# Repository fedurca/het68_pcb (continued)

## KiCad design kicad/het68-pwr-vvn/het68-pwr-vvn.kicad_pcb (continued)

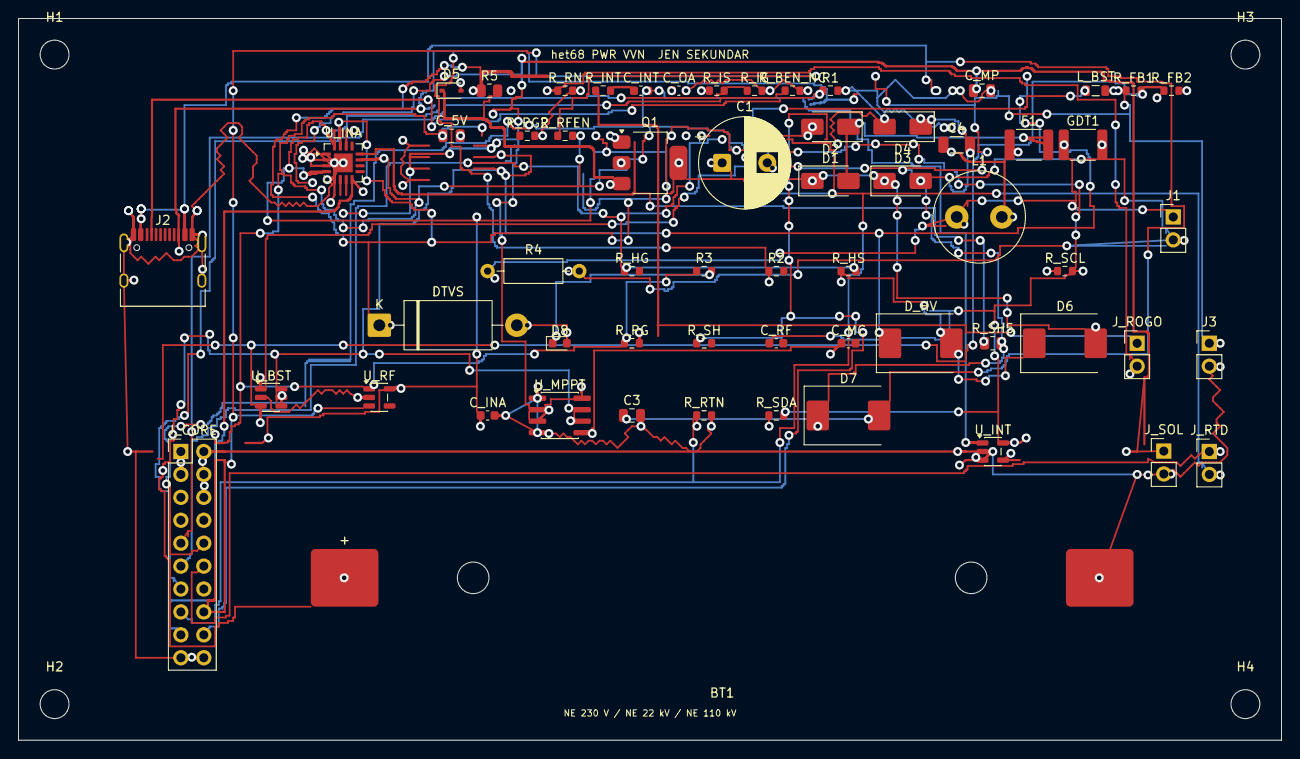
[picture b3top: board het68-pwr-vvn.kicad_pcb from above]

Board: 2 copper layers, 140.0 x 80.0 mm, 64 parts (0 on the bottom side), 35 nets.

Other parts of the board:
H1, H2, H3, H4: M3; MountingHole_3.2mm_M3

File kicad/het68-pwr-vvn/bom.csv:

Ref,Value,Footprint,MPN,LCSC
J1,CT_SEC,Connector_PinHeader_2.54mm:PinHeader_1x02_P2.54mm_Vertical,"sekundar CT, NE sit",
R4,100,Resistor_THT:R_Axial_DIN0207_L6.3mm_D2.5mm_P10.16mm_Horizontal,100R THT burden,
GDT1,GDT,Fuse:Fuse_1812_4532Metric,GDT secondary,
L1,470uH,Inductor_THT:L_Radial_D10.0mm_P5.00mm_Fastron_07P,470uH radial,
C4,1u/100V,Capacitor_SMD:C_1206_3216Metric,1uF 100V X7R LC,
F1,0.5A,Fuse:Fuse_1812_4532Metric,polyfuse 1812 0.5 A,
D1,SS14,Diode_SMD:D_SMA,SS14,
D2,SS14,Diode_SMD:D_SMA,SS14,
D3,SS14,Diode_SMD:D_SMA,SS14,
D4,SS14,Diode_SMD:D_SMA,SS14,
C1,470u/50V,Capacitor_THT:CP_Radial_D10.0mm_P5.00mm,electrolytic 470u 50V,
Q1,X0202MN,Package_TO_SOT_SMD:SOT-223,X0202MN,
D5,BZX84-C24,Diode_SMD:D_SOD-323,BZX84-C24,
R5,1k,Resistor_SMD:R_0805_2012Metric,RC0805FR-071KL,
DTVS,15KP36A,Diode_THT:D_DO-201_P15.24mm_Horizontal,15KP36A,
D6,SS34,Diode_SMD:D_SMC,SS34,
J_ROGO,ROGOWSKI,Connector_PinHeader_2.54mm:PinHeader_1x02_P2.54mm_Vertical,"Rogowski secondary, NE sit",
R_RN,0,Resistor_SMD:R_0603_1608Metric,RC0603FR-070RL,
R_INT,10k,Resistor_SMD:R_0603_1608Metric,RC0603FR-0710KL,
C_INT,100n,Capacitor_SMD:C_0603_1608Metric,CL10B104KB8NNNC,
U_INT,MCP6001,Package_TO_SOT_SMD:SOT-23-5,MCP6001T-OT,
C_OA,100n,Capacitor_SMD:C_0603_1608Metric,CL10B104KB8NNNC,
R_IS,10k,Resistor_SMD:R_0603_1608Metric,RC0603FR-0710KL,
R_IG,10k,Resistor_SMD:R_0603_1608Metric,RC0603FR-0710KL,
R_BEN_NC,100k,Resistor_SMD:R_0603_1608Metric,RC0603FR-07100KL,
J2,USB_C,Connector_USB:USB_C_Receptacle_HRO_TYPE-C-31-M-12,TYPE-C-31-M-12,C165948
R1,5.1k,Resistor_SMD:R_0603_1608Metric,RC0603FR-075K1L,
R2,5.1k,Resistor_SMD:R_0603_1608Metric,RC0603FR-075K1L,
D7,SS34,Diode_SMD:D_SMC,SS34,
C3,10u,Capacitor_SMD:C_0805_2012Metric,CL21A106KOQNNNE,
J_SOL,SOLAR,Connector_PinHeader_2.54mm:PinHeader_1x02_P2.54mm_Vertical,panel Voc 6-18 V,
U_MPPT,CN3791,Package_SO:SOIC-8_3.9x4.9mm_P1.27mm,CN3791,
C_MP,10u,Capacitor_SMD:C_0805_2012Metric,CL21A106KOQNNNE,
C_MC,100n,Capacitor_SMD:C_0603_1608Metric,CL10B104KB8NNNC,
D_HV,SS34,Diode_SMD:D_SMC,SS34,
BT1,21700,het68:Keystone_1122_21700,Keystone 1122,
U_BST,FP6291,Package_TO_SOT_SMD:SOT-23-6,FP6291,
L_BST,10uH,Inductor_SMD:L_0805_2012Metric,10uH boost,
R_FB1,100k,Resistor_SMD:R_0603_1608Metric,RC0603FR-07100KL,
R_FB2,20k,Resistor_SMD:R_0603_1608Metric,RC0603FR-0720KL,
C_5V,10u,Capacitor_SMD:C_0805_2012Metric,CL21A106KOQNNNE,
R_PG,10k,Resistor_SMD:R_0603_1608Metric,RC0603FR-0710KL,
R_PG2,10k,Resistor_SMD:R_0603_1608Metric,RC0603FR-0710KL,
U_RF,AP2112K-3.3,Package_TO_SOT_SMD:SOT-23-5,AP2112K-3.3TRG1,
R_RFEN,10k,Resistor_SMD:R_0603_1608Metric,RC0603FR-0710KL,
C_RF,1u,Capacitor_SMD:C_0603_1608Metric,CL10A105KA8NNNC,
U_INA,INA3221,Package_DFN_QFN:Texas_RGV0016A_VQFN-16-1EP_4x4mm_P0.65mm_EP2.1x2.1mm,INA3221AIRGVR,C181255
R_SH5,0.1,Resistor_SMD:R_0805_2012Metric,RC0805FR-070R1L,
C_INA,100n,Capacitor_SMD:C_0603_1608Metric,CL10B104KB8NNNC,
R_HS,10k,Resistor_SMD:R_0603_1608Metric,RC0603FR-0710KL,
R_HG,10k,Resistor_SMD:R_0603_1608Metric,RC0603FR-0710KL,
J_RTD,PT1000,Connector_PinHeader_2.54mm:PinHeader_1x02_P2.54mm_Vertical,PT1000 on conductor,
R_RTN,0,Resistor_SMD:R_0603_1608Metric,RC0603FR-070RL,
J_CORE,J_CORE,Connector_PinHeader_2.54mm:PinHeader_2x10_P2.54mm_Vertical,interconnect 2x10,
R_SH,0,Resistor_SMD:R_0603_1608Metric,RC0603FR-070RL,
R_SDA,4.7k,Resistor_SMD:R_0603_1608Metric,RC0603FR-074K7L,
R_SCL,4.7k,Resistor_SMD:R_0603_1608Metric,RC0603FR-074K7L,
D8,LED,LED_SMD:LED_0603_1608Metric,LED 0603,
R3,2.2k,Resistor_SMD:R_0603_1608Metric,RC0603FR-072K2L,
J3,VOUT,Connector_PinHeader_2.54mm:PinHeader_1x02_P2.54mm_Vertical,5V lab,

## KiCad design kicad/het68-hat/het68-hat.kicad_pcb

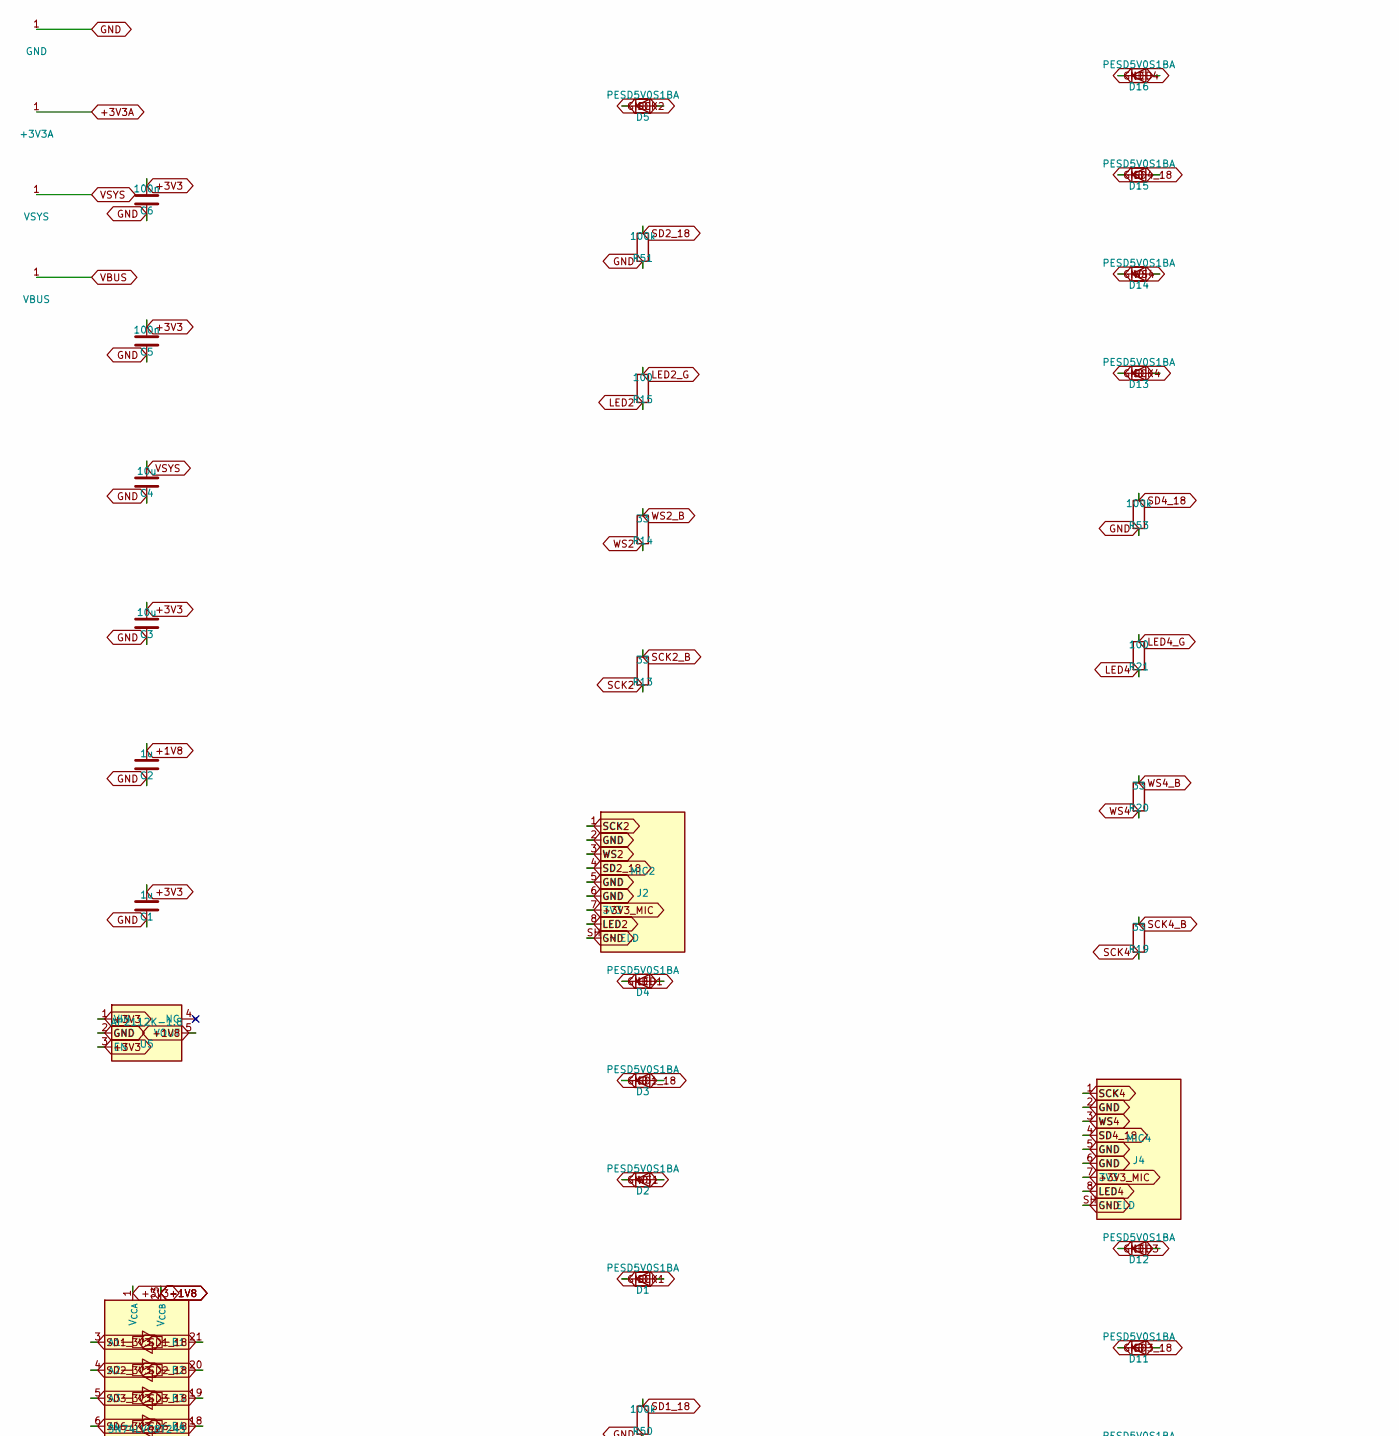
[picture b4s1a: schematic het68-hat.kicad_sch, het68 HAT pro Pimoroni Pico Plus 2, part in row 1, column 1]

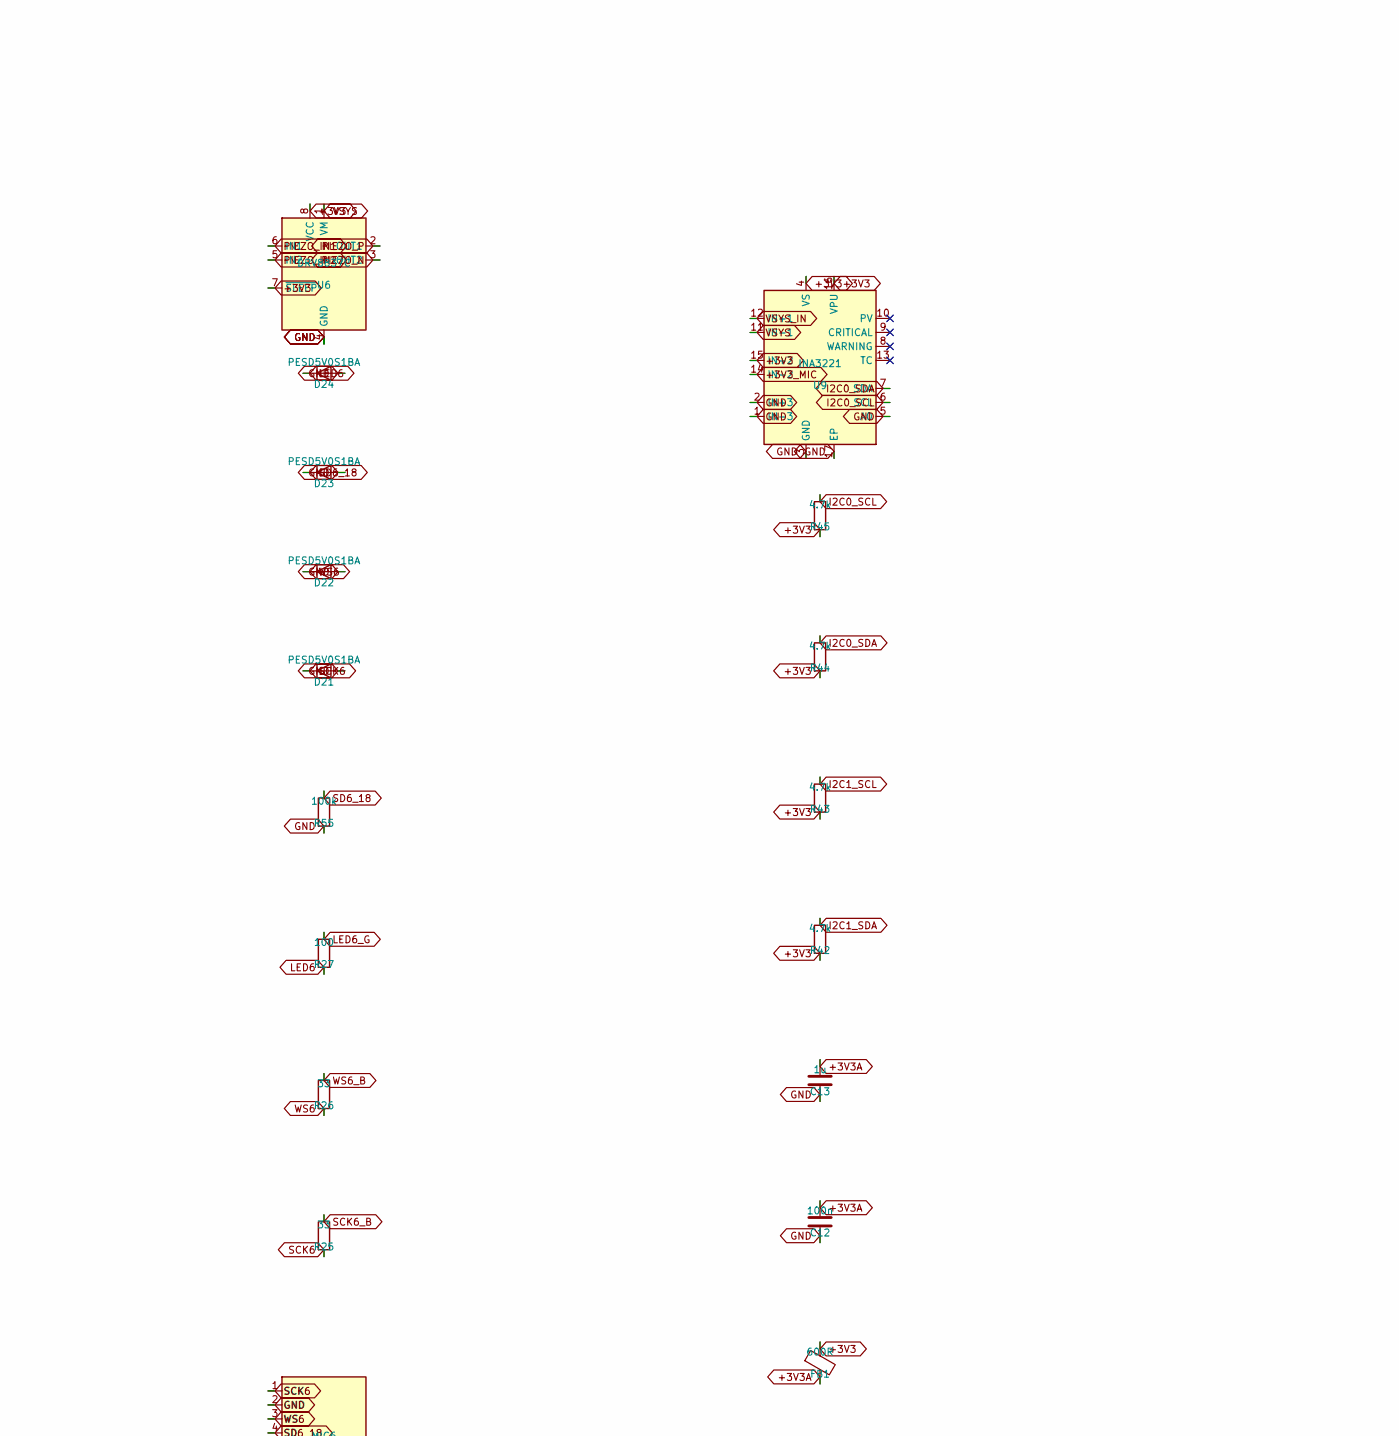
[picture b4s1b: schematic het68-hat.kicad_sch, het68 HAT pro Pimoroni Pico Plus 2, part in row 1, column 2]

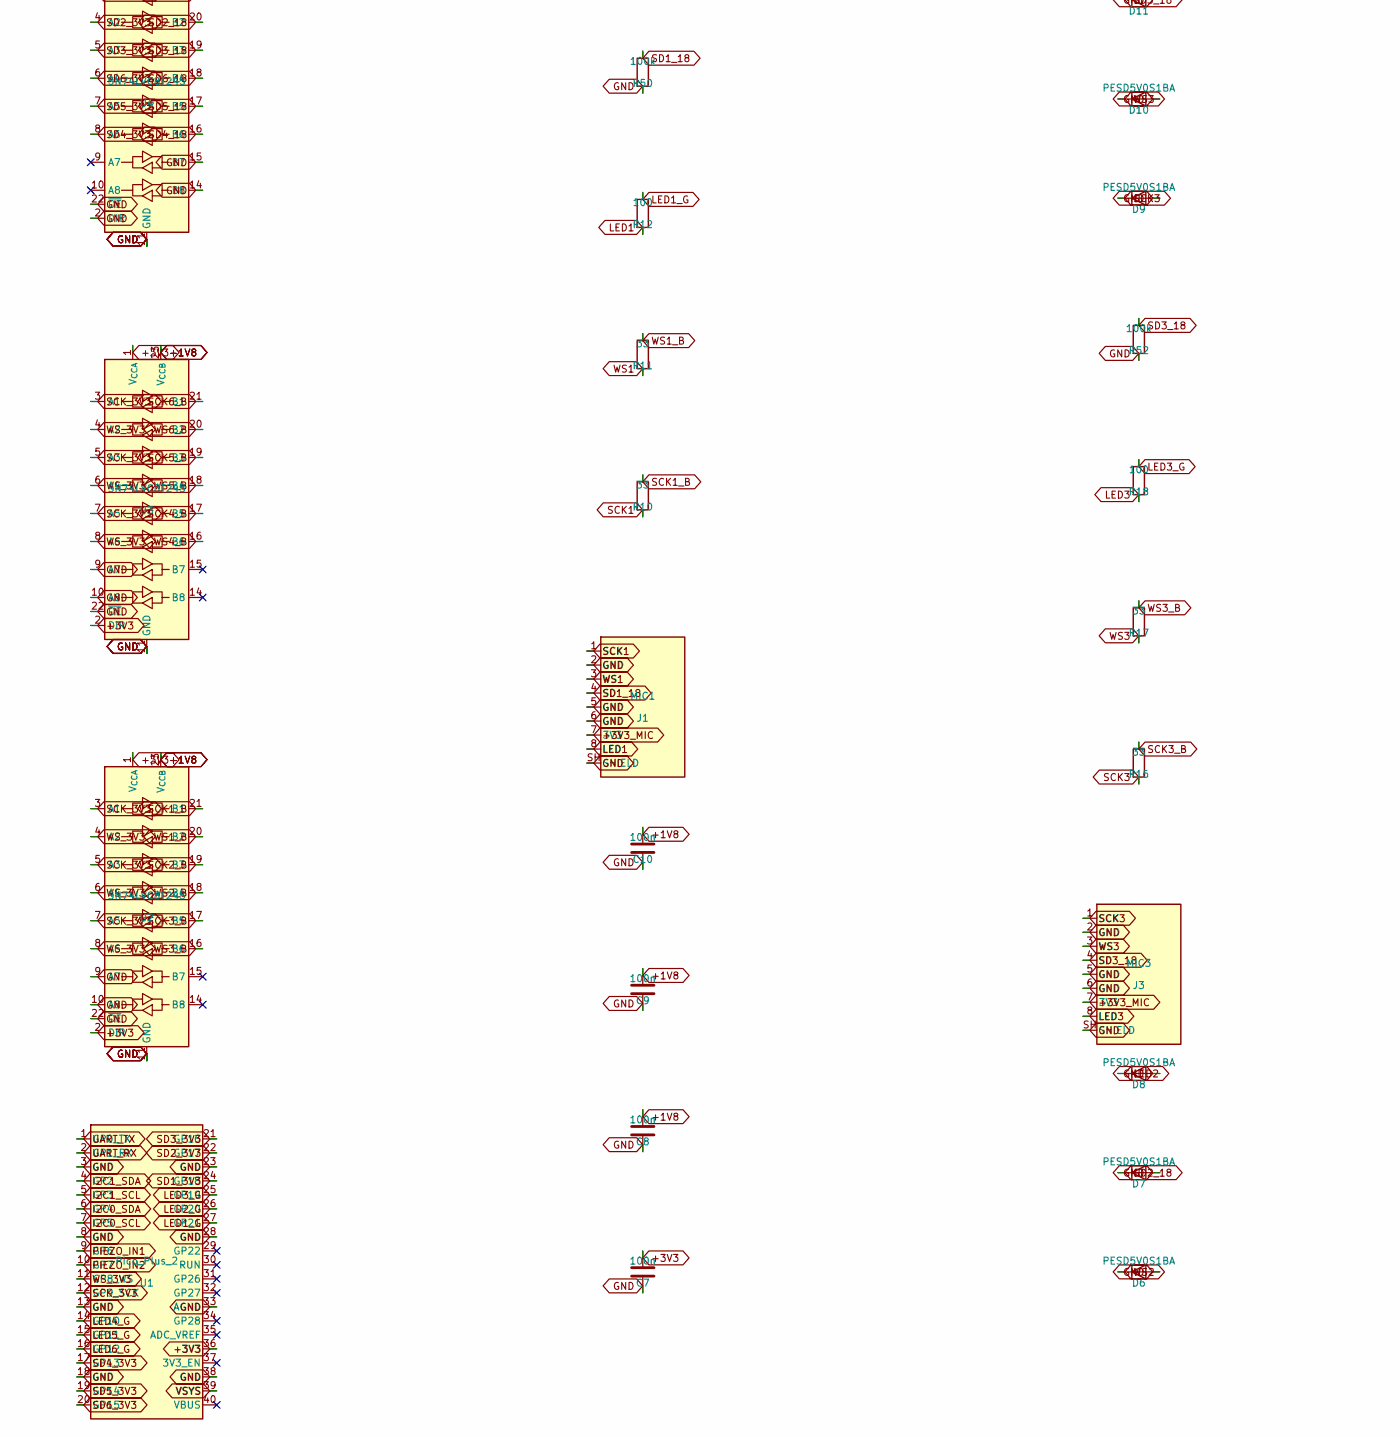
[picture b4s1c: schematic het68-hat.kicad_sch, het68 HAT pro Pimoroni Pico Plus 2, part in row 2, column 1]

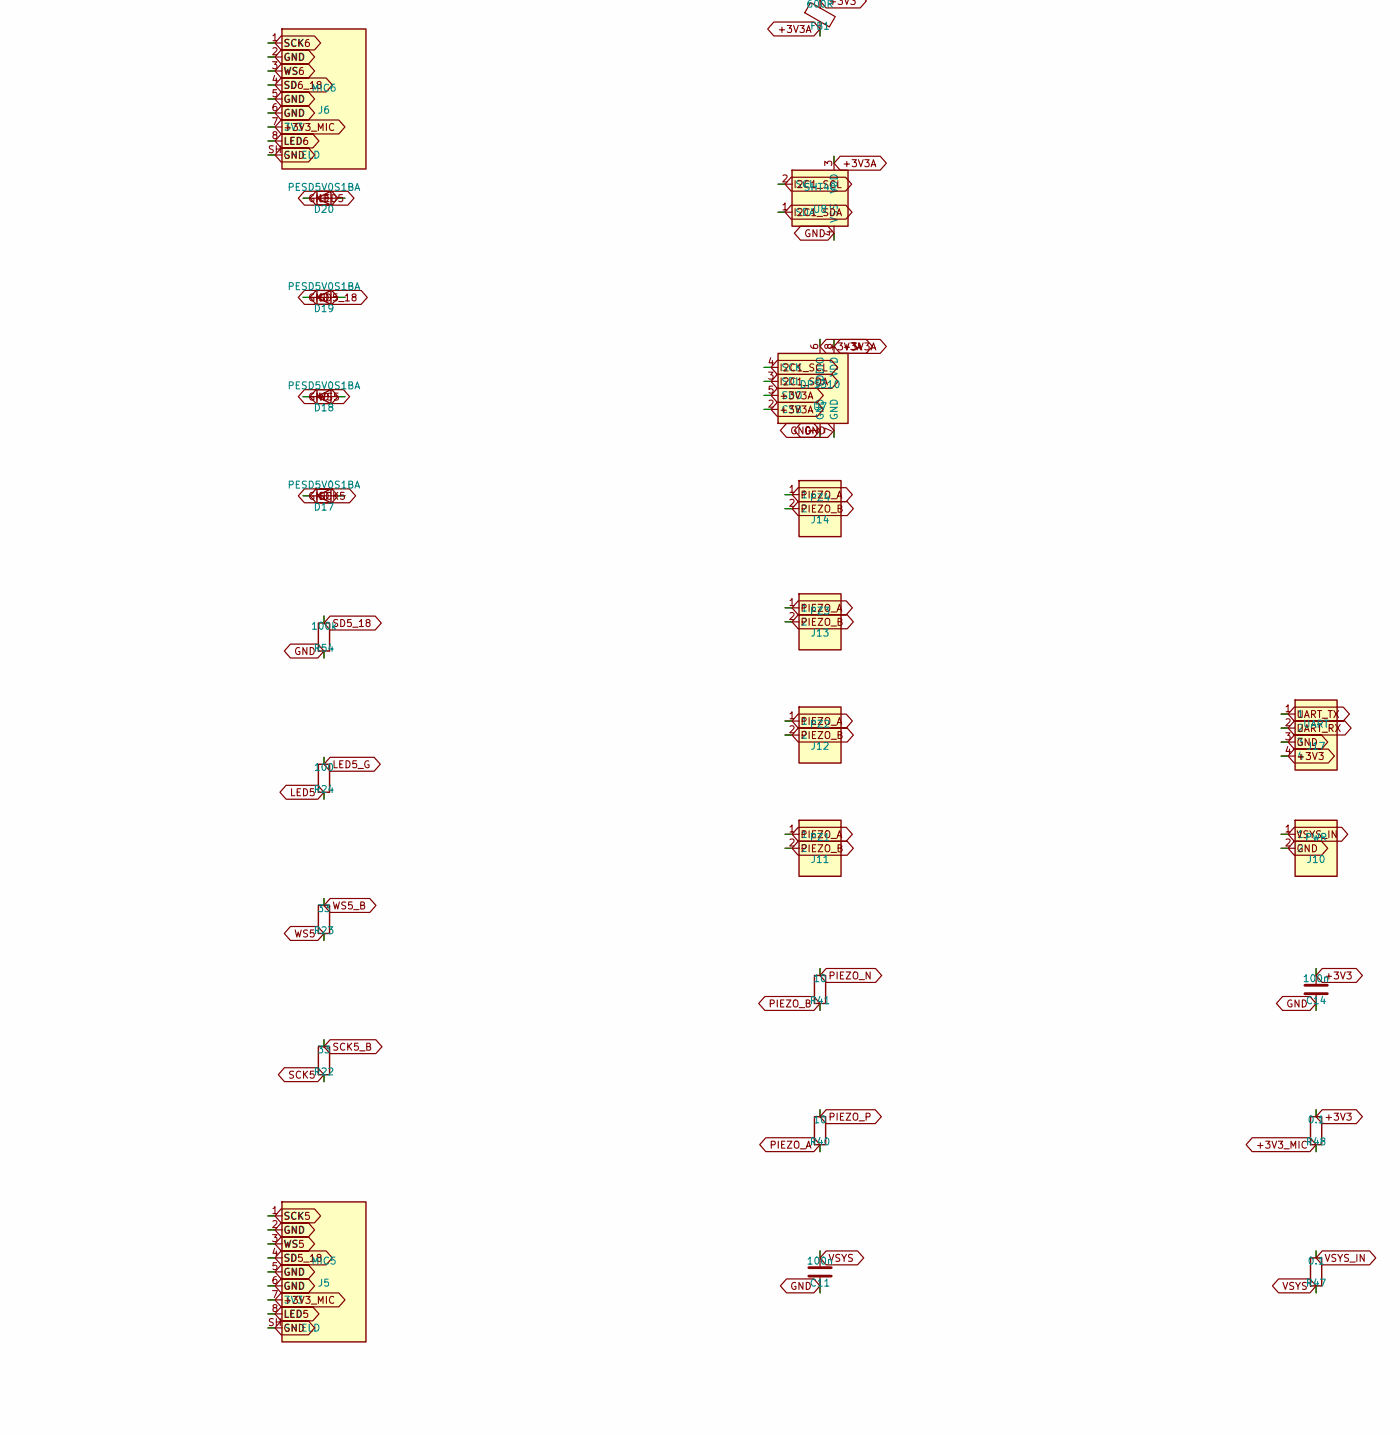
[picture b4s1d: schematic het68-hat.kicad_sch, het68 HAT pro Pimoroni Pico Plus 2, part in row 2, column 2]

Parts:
C1, C2, C13: 1u; C_0603_1608Metric; MPN CL10A105KA8NNNC
C3, C4: 10u; C_0805_2012Metric; MPN CL21A106KOQNNNE
C5, C6, C7, C8, C9, C10, C11, C12, C14: 100n; C_0603_1608Metric; MPN CL10B104KB8NNNC
D1, D2, D3, D4, D5, D6, D7, D8, D9, D10, D11, D12, D13, D14, D15, D16, D17, D18, D19, D20, D21, D22, D23, D24: PESD5V0S1BA; D_SOD-323; MPN PESD5V0S1BA,115
FB1: 600R; L_0603_1608Metric; MPN BLM18PG601SN1D
J1: MIC1; RJ45_RJHSE5380_het68; MPN RJHSE-5380 (8P8C, bez magnetik)
J2: MIC2; RJ45_RJHSE5380_het68; MPN RJHSE-5380 (8P8C, bez magnetik)
J3: MIC3; RJ45_RJHSE5380_het68; MPN RJHSE-5380 (8P8C, bez magnetik)
J4: MIC4; RJ45_RJHSE5380_het68; MPN RJHSE-5380 (8P8C, bez magnetik)
J5: MIC5; RJ45_RJHSE5380_het68; MPN RJHSE-5380 (8P8C, bez magnetik)
J6: MIC6; RJ45_RJHSE5380_het68; MPN RJHSE-5380 (8P8C, bez magnetik)
J10: PWR; PinHeader_1x02_P2.54mm_Vertical; MPN PinHeader 1x2
J11: PZ1; PinHeader_1x02_P2.54mm_Vertical; MPN PinHeader 1x2
J12: PZ2; PinHeader_1x02_P2.54mm_Vertical; MPN PinHeader 1x2
J13: PZ3; PinHeader_1x02_P2.54mm_Vertical; MPN PinHeader 1x2
J14: PZ4; PinHeader_1x02_P2.54mm_Vertical; MPN PinHeader 1x2
J17: UART; PinHeader_1x04_P2.54mm_Vertical; MPN PinHeader 1x4
R10, R11, R13, R14, R16, R17, R19, R20, R22, R23, R25, R26: 33; R_0603_1608Metric; MPN RC0603FR-0733RL
R12, R15, R18, R21, R24, R27: 100; R_0603_1608Metric; MPN RC0603FR-07100RL
R40, R41: 10; R_1206_3216Metric; MPN RC1206FR-0710RL
R42, R43, R44, R45: 4.7k; R_0603_1608Metric; MPN RC0603FR-074K7L
R47, R48: 0.1; R_0805_2012Metric; MPN RC0805FR-070R1L
R50, R51, R52, R53, R54, R55: 100k; R_0603_1608Metric; MPN RC0603FR-07100KL
U1: Pico_Plus_2; RaspberryPi_Pico_Common_THT; MPN Pimoroni Pico Plus 2
U2, U3, U4: SN74LVC8T245; TSSOP-24_4.4x7.8mm_P0.65mm; MPN SN74LVC8T245PWR
U5: AP2112K-1.8; SOT-23-5; MPN AP2112K-1.8TRG1
U6: DRV8837C; Texas_DSG0008A_WSON-8-1EP_2x2mm_P0.5mm_EP0.9x1.6mm; MPN DRV8837CDSGR
U7: DPS310; Bosch_LGA-8_2x2.5mm_P0.65mm_ClockwisePinNumbering; MPN DPS310
U8: SHT40; Sensirion_DFN-4_1.5x1.5mm_P0.8mm_SHT4x_NoCentralPad; MPN SHT40-AD1B-R2
U9: INA3221; Texas_RGV0016A_VQFN-16-1EP_4x4mm_P0.65mm_EP2.1x2.1mm; MPN INA3221AIRGVR

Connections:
+1V8: C2.1, C8.1, C9.1, C10.1, U2.23 (V_{CCB}), U2.24 (V_{CCB}), U3.23 (V_{CCB}), U3.24 (V_{CCB}), U4.23 (V_{CCB}), U4.24 (V_{CCB}), U5.5 (VOUT)
+3V3: C1.1, C3.1, C5.1, C6.1, C7.1, C14.1, FB1.1, J17.4, R42.2, R43.2, R44.2, R45.2, R48.1, U1.36 (3V3), U2.1 (V_{CCA}), U2.2 (DIR), U3.1 (V_{CCA}), U3.2 (DIR), U4.1 (V_{CCA}), U5.1 (VIN), U5.3 (EN), U6.7 (~SLEEP), U6.8 (VCC), U9.4 (VS), U9.15 (IN+2), U9.16 (VPU)
+3V3A: C12.1, C13.1, FB1.2, U7.2 (CSB), U7.5 (SDO), U7.6 (VDDIO), U7.8 (VDD), U8.3 (VDD)
+3V3_MIC: J1.7 (3V3), J2.7 (3V3), J3.7 (3V3), J4.7 (3V3), J5.7 (3V3), J6.7 (3V3), R48.2, U9.14 (IN-2)
GND: C1.2, C2.2, C3.2, C4.2, C5.2, C6.2, C7.2, C8.2, C9.2, C10.2, C11.2, C12.2, C13.2, C14.2, D1.2 (A), D2.2 (A), D3.2 (A), D4.2 (A), D5.2 (A), D6.2 (A), D7.2 (A), D8.2 (A), D9.2 (A), D10.2 (A), D11.2 (A), D12.2 (A), D13.2 (A), D14.2 (A), D15.2 (A), D16.2 (A), D17.2 (A), D18.2 (A), D19.2 (A), D20.2 (A), D21.2 (A), D22.2 (A), D23.2 (A), D24.2 (A), J1.2 (GND), J1.5 (GND), J1.6 (GND), J1.SH (SHIELD), J2.2 (GND), J2.5 (GND), J2.6 (GND), J2.SH (SHIELD), J3.2 (GND), J3.5 (GND), J3.6 (GND), J3.SH (SHIELD), J4.2 (GND), J4.5 (GND), J4.6 (GND), J4.SH (SHIELD), J5.2 (GND), J5.5 (GND), J5.6 (GND), J5.SH (SHIELD), J6.2 (GND), J6.5 (GND), J6.6 (GND), J6.SH (SHIELD), J10.2, J17.3, R50.2, R51.2, R52.2, R53.2, R54.2, R55.2, U1.3 (GND), U1.8 (GND), U1.13 (GND), U1.18 (GND), U1.23 (GND), U1.28 (GND), U1.33 (AGND), U1.38 (GND), U2.9 (A7), U2.10 (A8), U2.11 (GND), U2.12 (GND), U2.13 (GND), U2.22 (~OE), U3.9 (A7), U3.10 (A8), U3.11 (GND), U3.12 (GND), U3.13 (GND), U3.22 (~OE), U4.2 (DIR), U4.11 (GND), U4.12 (GND), U4.13 (GND), U4.14 (B8), U4.15 (B7), U4.22 (~OE), U5.2 (GND), U6.4 (GND), U6.9 (GND), U7.1 (GND), U7.7 (GND), U8.4 (VSS), U9.1 (IN-3), U9.2 (IN+3), U9.3 (GND), U9.5 (A0), U9.17 (EP)
I2C0_SCL: R45.1, U1.7 (GP5), U9.6 (SCL)
I2C0_SDA: R44.1, U1.6 (GP4), U9.7 (SDA)
I2C1_SCL: R43.1, U1.5 (GP3), U7.4 (SCK), U8.2 (SCL)
I2C1_SDA: R42.1, U1.4 (GP2), U7.3 (SDI), U8.1 (SDA)
LED1: D4.1 (K), J1.8 (LED), R12.2
LED1_G: R12.1, U1.27 (GP21)
LED2: D8.1 (K), J2.8 (LED), R15.2
LED2_G: R15.1, U1.26 (GP20)
LED3: D12.1 (K), J3.8 (LED), R18.2
LED3_G: R18.1, U1.25 (GP19)
LED4: D16.1 (K), J4.8 (LED), R21.2
LED4_G: R21.1, U1.14 (GP10)
LED5: D20.1 (K), J5.8 (LED), R24.2
LED5_G: R24.1, U1.15 (GP11)
LED6: D24.1 (K), J6.8 (LED), R27.2
LED6_G: R27.1, U1.16 (GP12)
PIEZO_A: J11.1, J12.1, J13.1, J14.1, R40.2
PIEZO_B: J11.2, J12.2, J13.2, J14.2, R41.2
PIEZO_IN1: U1.9 (GP6), U6.6 (IN1)
PIEZO_IN2: U1.10 (GP7), U6.5 (IN2)
PIEZO_N: R41.1, U6.3 (OUT2)
PIEZO_P: R40.1, U6.2 (OUT1)
SCK1: D1.1 (K), J1.1 (SCK), R10.2
SCK1_B: R10.1, U2.21 (B1)
SCK2: D5.1 (K), J2.1 (SCK), R13.2
SCK2_B: R13.1, U2.19 (B3)
SCK3: D9.1 (K), J3.1 (SCK), R16.2
SCK3_B: R16.1, U2.17 (B5)
SCK4: D13.1 (K), J4.1 (SCK), R19.2
SCK4_B: R19.1, U3.17 (B5)
SCK5: D17.1 (K), J5.1 (SCK), R22.2
SCK5_B: R22.1, U3.19 (B3)
SCK6: D21.1 (K), J6.1 (SCK), R25.2
SCK6_B: R25.1, U3.21 (B1)
SCK_3V3: U1.12 (GP9_SCK), U2.3 (A1), U2.5 (A3), U2.7 (A5), U3.3 (A1), U3.5 (A3), U3.7 (A5)
SD1_3V3: U1.24 (GP18), U4.3 (A1)
SD1_18: D3.1 (K), J1.4 (SD), R50.1, U4.21 (B1)
SD2_3V3: U1.22 (GP17), U4.4 (A2)
SD2_18: D7.1 (K), J2.4 (SD), R51.1, U4.20 (B2)
SD3_3V3: U1.21 (GP16), U4.5 (A3)
SD3_18: D11.1 (K), J3.4 (SD), R52.1, U4.19 (B3)
SD4_3V3: U1.17 (GP13), U4.8 (A6)
SD4_18: D15.1 (K), J4.4 (SD), R53.1, U4.16 (B6)
SD5_3V3: U1.19 (GP14), U4.7 (A5)
SD5_18: D19.1 (K), J5.4 (SD), R54.1, U4.17 (B5)
SD6_3V3: U1.20 (GP15), U4.6 (A4)
SD6_18: D23.1 (K), J6.4 (SD), R55.1, U4.18 (B4)
UART_RX: J17.2, U1.2 (GP1_RX)
UART_TX: J17.1, U1.1 (GP0_TX)
VSYS: C4.1, C11.1, R47.2, U1.39 (VSYS), U6.1 (VM), U9.11 (IN-1)
VSYS_IN: J10.1, R47.1, U9.12 (IN+1)
WS1: D2.1 (K), J1.3 (WS), R11.2
WS1_B: R11.1, U2.20 (B2)
WS2: D6.1 (K), J2.3 (WS), R14.2
WS2_B: R14.1, U2.18 (B4)
WS3: D10.1 (K), J3.3 (WS), R17.2
WS3_B: R17.1, U2.16 (B6)
WS4: D14.1 (K), J4.3 (WS), R20.2
WS4_B: R20.1, U3.16 (B6)
WS5: D18.1 (K), J5.3 (WS), R23.2
WS5_B: R23.1, U3.18 (B4)
WS6: D22.1 (K), J6.3 (WS), R26.2
WS6_B: R26.1, U3.20 (B2)
WS_3V3: U1.11 (GP8_WS), U2.4 (A2), U2.6 (A4), U2.8 (A6), U3.4 (A2), U3.6 (A4), U3.8 (A6)

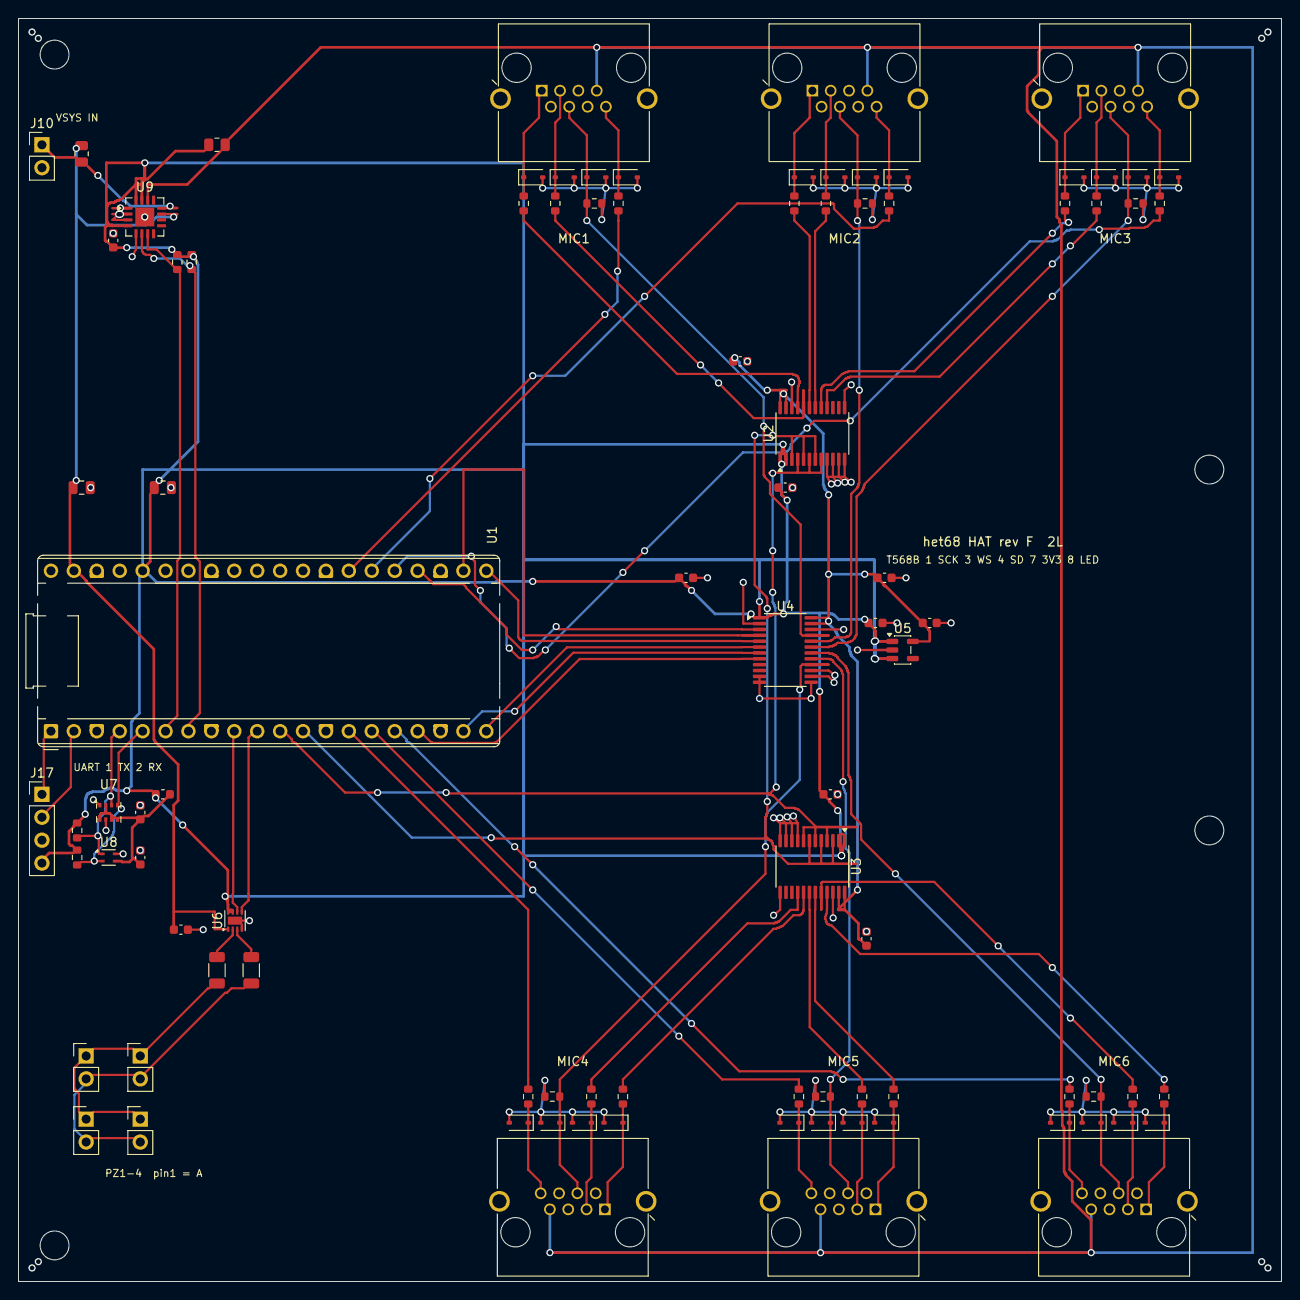
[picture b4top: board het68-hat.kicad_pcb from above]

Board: 2 copper layers, 140.0 x 140.0 mm, 96 parts (0 on the bottom side), 69 nets.

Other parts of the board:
H1, H2, H3, H4: M3; MountingHole_3.2mm_M3

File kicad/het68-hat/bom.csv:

Ref,Value,Footprint,MPN,LCSC
U1,Pico_Plus_2,Module:RaspberryPi_Pico_Common_THT,Pimoroni Pico Plus 2,
U2,SN74LVC8T245,Package_SO:TSSOP-24_4.4x7.8mm_P0.65mm,SN74LVC8T245PWR,C27643
U3,SN74LVC8T245,Package_SO:TSSOP-24_4.4x7.8mm_P0.65mm,SN74LVC8T245PWR,C27643
U4,SN74LVC8T245,Package_SO:TSSOP-24_4.4x7.8mm_P0.65mm,SN74LVC8T245PWR,C27643
U5,AP2112K-1.8,Package_TO_SOT_SMD:SOT-23-5,AP2112K-1.8TRG1,C176944
C1,1u,Capacitor_SMD:C_0603_1608Metric,CL10A105KA8NNNC,
C2,1u,Capacitor_SMD:C_0603_1608Metric,CL10A105KA8NNNC,
C3,10u,Capacitor_SMD:C_0805_2012Metric,CL21A106KOQNNNE,
C4,10u,Capacitor_SMD:C_0805_2012Metric,CL21A106KOQNNNE,
C5,100n,Capacitor_SMD:C_0603_1608Metric,CL10B104KB8NNNC,
C6,100n,Capacitor_SMD:C_0603_1608Metric,CL10B104KB8NNNC,
C7,100n,Capacitor_SMD:C_0603_1608Metric,CL10B104KB8NNNC,
C8,100n,Capacitor_SMD:C_0603_1608Metric,CL10B104KB8NNNC,
C9,100n,Capacitor_SMD:C_0603_1608Metric,CL10B104KB8NNNC,
C10,100n,Capacitor_SMD:C_0603_1608Metric,CL10B104KB8NNNC,
J1,MIC1,het68:RJ45_RJHSE5380_het68,"RJHSE-5380 (8P8C, bez magnetik)",C464586
R10,33,Resistor_SMD:R_0603_1608Metric,RC0603FR-0733RL,
R11,33,Resistor_SMD:R_0603_1608Metric,RC0603FR-0733RL,
R12,100,Resistor_SMD:R_0603_1608Metric,RC0603FR-07100RL,
R50,100k,Resistor_SMD:R_0603_1608Metric,RC0603FR-07100KL,
D1,PESD5V0S1BA,Diode_SMD:D_SOD-323,"PESD5V0S1BA,115",
D2,PESD5V0S1BA,Diode_SMD:D_SOD-323,"PESD5V0S1BA,115",
D3,PESD5V0S1BA,Diode_SMD:D_SOD-323,"PESD5V0S1BA,115",
D4,PESD5V0S1BA,Diode_SMD:D_SOD-323,"PESD5V0S1BA,115",
J2,MIC2,het68:RJ45_RJHSE5380_het68,"RJHSE-5380 (8P8C, bez magnetik)",C464586
R13,33,Resistor_SMD:R_0603_1608Metric,RC0603FR-0733RL,
R14,33,Resistor_SMD:R_0603_1608Metric,RC0603FR-0733RL,
R15,100,Resistor_SMD:R_0603_1608Metric,RC0603FR-07100RL,
R51,100k,Resistor_SMD:R_0603_1608Metric,RC0603FR-07100KL,
D5,PESD5V0S1BA,Diode_SMD:D_SOD-323,"PESD5V0S1BA,115",
D6,PESD5V0S1BA,Diode_SMD:D_SOD-323,"PESD5V0S1BA,115",
D7,PESD5V0S1BA,Diode_SMD:D_SOD-323,"PESD5V0S1BA,115",
D8,PESD5V0S1BA,Diode_SMD:D_SOD-323,"PESD5V0S1BA,115",
J3,MIC3,het68:RJ45_RJHSE5380_het68,"RJHSE-5380 (8P8C, bez magnetik)",C464586
R16,33,Resistor_SMD:R_0603_1608Metric,RC0603FR-0733RL,
R17,33,Resistor_SMD:R_0603_1608Metric,RC0603FR-0733RL,
R18,100,Resistor_SMD:R_0603_1608Metric,RC0603FR-07100RL,
R52,100k,Resistor_SMD:R_0603_1608Metric,RC0603FR-07100KL,
D9,PESD5V0S1BA,Diode_SMD:D_SOD-323,"PESD5V0S1BA,115",
D10,PESD5V0S1BA,Diode_SMD:D_SOD-323,"PESD5V0S1BA,115",
D11,PESD5V0S1BA,Diode_SMD:D_SOD-323,"PESD5V0S1BA,115",
D12,PESD5V0S1BA,Diode_SMD:D_SOD-323,"PESD5V0S1BA,115",
J4,MIC4,het68:RJ45_RJHSE5380_het68,"RJHSE-5380 (8P8C, bez magnetik)",C464586
R19,33,Resistor_SMD:R_0603_1608Metric,RC0603FR-0733RL,
R20,33,Resistor_SMD:R_0603_1608Metric,RC0603FR-0733RL,
R21,100,Resistor_SMD:R_0603_1608Metric,RC0603FR-07100RL,
R53,100k,Resistor_SMD:R_0603_1608Metric,RC0603FR-07100KL,
D13,PESD5V0S1BA,Diode_SMD:D_SOD-323,"PESD5V0S1BA,115",
D14,PESD5V0S1BA,Diode_SMD:D_SOD-323,"PESD5V0S1BA,115",
D15,PESD5V0S1BA,Diode_SMD:D_SOD-323,"PESD5V0S1BA,115",
D16,PESD5V0S1BA,Diode_SMD:D_SOD-323,"PESD5V0S1BA,115",
J5,MIC5,het68:RJ45_RJHSE5380_het68,"RJHSE-5380 (8P8C, bez magnetik)",C464586
R22,33,Resistor_SMD:R_0603_1608Metric,RC0603FR-0733RL,
R23,33,Resistor_SMD:R_0603_1608Metric,RC0603FR-0733RL,
R24,100,Resistor_SMD:R_0603_1608Metric,RC0603FR-07100RL,
R54,100k,Resistor_SMD:R_0603_1608Metric,RC0603FR-07100KL,
D17,PESD5V0S1BA,Diode_SMD:D_SOD-323,"PESD5V0S1BA,115",
D18,PESD5V0S1BA,Diode_SMD:D_SOD-323,"PESD5V0S1BA,115",
D19,PESD5V0S1BA,Diode_SMD:D_SOD-323,"PESD5V0S1BA,115",
D20,PESD5V0S1BA,Diode_SMD:D_SOD-323,"PESD5V0S1BA,115",
J6,MIC6,het68:RJ45_RJHSE5380_het68,"RJHSE-5380 (8P8C, bez magnetik)",C464586
R25,33,Resistor_SMD:R_0603_1608Metric,RC0603FR-0733RL,
R26,33,Resistor_SMD:R_0603_1608Metric,RC0603FR-0733RL,
R27,100,Resistor_SMD:R_0603_1608Metric,RC0603FR-07100RL,
R55,100k,Resistor_SMD:R_0603_1608Metric,RC0603FR-07100KL,
D21,PESD5V0S1BA,Diode_SMD:D_SOD-323,"PESD5V0S1BA,115",
D22,PESD5V0S1BA,Diode_SMD:D_SOD-323,"PESD5V0S1BA,115",
D23,PESD5V0S1BA,Diode_SMD:D_SOD-323,"PESD5V0S1BA,115",
D24,PESD5V0S1BA,Diode_SMD:D_SOD-323,"PESD5V0S1BA,115",
U6,DRV8837C,Package_SON:Texas_DSG0008A_WSON-8-1EP_2x2mm_P0.5mm_EP0.9x1.6mm,DRV8837CDSGR,C191000
C11,100n,Capacitor_SMD:C_0603_1608Metric,CL10B104KB8NNNC,
R40,10,Resistor_SMD:R_1206_3216Metric,RC1206FR-0710RL,
R41,10,Resistor_SMD:R_1206_3216Metric,RC1206FR-0710RL,
J11,PZ1,Connector_PinHeader_2.54mm:PinHeader_1x02_P2.54mm_Vertical,PinHeader 1x2,
J12,PZ2,Connector_PinHeader_2.54mm:PinHeader_1x02_P2.54mm_Vertical,PinHeader 1x2,
J13,PZ3,Connector_PinHeader_2.54mm:PinHeader_1x02_P2.54mm_Vertical,PinHeader 1x2,
J14,PZ4,Connector_PinHeader_2.54mm:PinHeader_1x02_P2.54mm_Vertical,PinHeader 1x2,
U7,DPS310,Package_LGA:Bosch_LGA-8_2x2.5mm_P0.65mm_ClockwisePinNumbering,DPS310,C130156
U8,SHT40,Sensor_Humidity:Sensirion_DFN-4_1.5x1.5mm_P0.8mm_SHT4x_NoCentralPad,SHT40-AD1B-R2,C2909890
FB1,600R,Inductor_SMD:L_0603_1608Metric,BLM18PG601SN1D,
C12,100n,Capacitor_SMD:C_0603_1608Metric,CL10B104KB8NNNC,
C13,1u,Capacitor_SMD:C_0603_1608Metric,CL10A105KA8NNNC,
R42,4.7k,Resistor_SMD:R_0603_1608Metric,RC0603FR-074K7L,
R43,4.7k,Resistor_SMD:R_0603_1608Metric,RC0603FR-074K7L,
R44,4.7k,Resistor_SMD:R_0603_1608Metric,RC0603FR-074K7L,
R45,4.7k,Resistor_SMD:R_0603_1608Metric,RC0603FR-074K7L,
U9,INA3221,Package_DFN_QFN:Texas_RGV0016A_VQFN-16-1EP_4x4mm_P0.65mm_EP2.1x2.1mm,INA3221AIRGVR,C181255
R47,0.1,Resistor_SMD:R_0805_2012Metric,RC0805FR-070R1L,
R48,0.1,Resistor_SMD:R_0805_2012Metric,RC0805FR-070R1L,
C14,100n,Capacitor_SMD:C_0603_1608Metric,CL10B104KB8NNNC,
J10,PWR,Connector_PinHeader_2.54mm:PinHeader_1x02_P2.54mm_Vertical,PinHeader 1x2,
J17,UART,Connector_PinHeader_2.54mm:PinHeader_1x04_P2.54mm_Vertical,PinHeader 1x4,

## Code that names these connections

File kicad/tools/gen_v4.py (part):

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        "73": "QSPI_SD2", "74": "QSPI_SD1", "75": "QSPI_SS",
        "30": "XIN", "31": "XOUT", "33": "SWCLK", "34": "SWDIO", "35": "RUN",
        "81": "GND",
        GPIO_PAD[0]: "UART_TX_MCU", GPIO_PAD[1]: "UART_RX_MCU",
        GPIO_PAD[2]: "I2C1_SDA", GPIO_PAD[3]: "I2C1_SCL",
        GPIO_PAD[4]: "I2C0_SDA", GPIO_PAD[5]: "I2C0_SCL",
        GPIO_PAD[6]: "PIEZO_IN1", GPIO_PAD[7]: "PIEZO_IN2",
        GPIO_PAD[8]: "I2S_WS_MCU", GPIO_PAD[9]: "I2S_SCK_MCU",
        GPIO_PAD[10]: "LED4_DIN", GPIO_PAD[11]: "LED5_DIN", GPIO_PAD[12]: "LED6_DIN",
        GPIO_PAD[13]: "I2S_SD4", GPIO_PAD[14]: "I2S_SD5", GPIO_PAD[15]: "I2S_SD6",
        GPIO_PAD[16]: "I2S_SD3", GPIO_PAD[17]: "I2S_SD2", GPIO_PAD[18]: "I2S_SD1",
        GPIO_PAD[19]: "LED3_DIN", GPIO_PAD[20]: "LED2_DIN", GPIO_PAD[21]: "LED1_DIN",
        GPIO_PAD[22]: "DSP_AWAKE",
        GPIO_PAD[23]: "SPI0_SCK", GPIO_PAD[24]: "SPI0_MOSI", GPIO_PAD[25]: "SPI0_MISO",
        GPIO_PAD[26]: "ADC_I", GPIO_PAD[27]: "ADC_ROGO",
        GPIO_PAD[28]: "ADC_PT1000", GPIO_PAD[29]: "ADC_HARVEST",
        GPIO_PAD[30]: "SPI0_CS", GPIO_PAD[31]: "BURDEN_EN",
        GPIO_PAD[32]: "PSRAM_CE", GPIO_PAD[33]: "PSRAM_SO",
        GPIO_PAD[34]: "PSRAM_SI", GPIO_PAD[35]: "PSRAM_SCLK",
        GPIO_PAD[36]: "PG_5V",
        GPIO_PAD[37]: "STATUS_DIN",
        GPIO_PAD[38]: "BTN_USER",
    })
    return n

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                {"1": "BURDEN_EN", "2": "GND", "3": "CHG_G"}, "AO3400A")
        R(sch, "R_IS", ("DC", "ADC_I"), "10k", mpn="RC0603FR-0710KL")
        R(sch, "R_IG", ("ADC_I", "GND"), "10k", mpn="RC0603FR-0710KL")
        # ADC_ROGO unused: tie to GND so ERC/pin has a net
        R(sch, "R_ROGO_NC", ("ADC_ROGO", "GND"), "100k", mpn="RC0603FR-07100KL")
    else:
        sch.add("het68:Conn_1x02", "J_ROGO", "ROGOWSKI",
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

def sat_prewire(api):
    """Escape RJ45 pin 3 (WS_P) south between the 1.3 mm rear-row lands.

    T5848 north-row VDD/SD would otherwise stay boxed in after WS routes
    north from pad 1. SD runs north at pad 8 X to the U5 LVDS-side stub;
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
